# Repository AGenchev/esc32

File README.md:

# code taken from esc32, reworked to compile with GCC/freeware toolchain

I modified this and reformed the project... The goal - to compile with FOSS tools completely and to contain all source.
I put in a PCB hardware design to test it.
I probably have introduced new bugs.

First "problem": When I compiled with GCC, I got less CPU free time than the binary from esc32. Thus the control loop was closer to take 100% of the CPU time.
I considered this dangerous, because the control loop is timer-driven, e.t. in IRQ. Resolution path taken: to rewrite the control loop in integer. Most of it's done, RPM calculation is still in floating point though.

The ESC code is in <a href=https://github.com/AGenchev/esc32/tree/gelemod02/onboard>"onboard"</a> directory. <br/>
The <a href=https://github.com/AGenchev/esc32/tree/gelemod02/ground>"ground"</a> directory contains the utility which tunes the rpm PID and the current limiter PID. It does not work yet with my hardware as I have not modified it. Actually I use the ESC with current limiter turned off.

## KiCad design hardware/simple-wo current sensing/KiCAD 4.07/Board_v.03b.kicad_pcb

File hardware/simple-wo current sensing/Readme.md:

This was designed for a friend who wanted simplest design. Current sensing amplifier and shunt were removed.

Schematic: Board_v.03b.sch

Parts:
C1, C2, C6, C7, C13: 10uF/25v; MICROBUILDER__0805MP
C3: 100n; MICROBUILDER__0805MP
C4, C9, C10, C14: 100n; MICROBUILDER__0603MP
C5, C11, C15: 4.7uF/25v; MICROBUILDER__0805MP
C8, C12, C16: 10nF; MICROBUILDER__0805MP
C20: 4.7u; MICROBUILDER__0805MP
D1: 1N4007 sma; do214ac
D2, D3, D4: SCHOTTKY B0540W@SOD123; sod123
IC1, IC2, IC5: IR2110S; soic-16
J1: J40MM; GELE_V04_J40MM
J3: J5MM; JUMPER_05
J4, J5, J11: J15MM; JUMPER_15
J9: J10MM; JUMPER_10
J14, J15: GELE_V05_CON-20PIN-SMD-MANUALLY-BENT-FROM-NON-SMD
PHASE_C42: PHASE_C; STEVEMARPLE_PAD
R1, R2, R10, R21, R22: 8.2Ω; MICROBUILDER__0805MP
R3, R11, R23: 15kΩ 1%; MICROBUILDER__0805MP
R5, R6, R13, R14, R25, R26: 10kΩ; MICROBUILDER__0805MP
R7, R15, R27: 2.2kΩ 1%; MICROBUILDER__0805MP
R8, R20: 0; MICROBUILDER__0805MP
R9: 8.2; MICROBUILDER__0805MP
R28: 0Ω; MICROBUILDER__0805MP
R35: 10kΩ 1%; MICROBUILDER__0805MP
R36: 1.5kΩ 1%; MICROBUILDER__0805MP
U1: 78L05F; sot89
U$1, U$10, U$16: IRF8313; so-8
U$11, U$30: CON_HEADER_1X20; GELE.TMP_M1X20_SMD_2.54MM_0.1%5c%22_LONGTRACKS
U$36: BLUEPILL; MAPLEMINI_40-DIP-BLUE-PIL
VP_0, VP_1, VP_2, VP_3, VP_4, VP_5, VP_6, VP_7, VP_8, VP_9, VP_10, VP_11: VPDEV0; VPAD_VPAC0
V_MOTOR42: V_MOTOR; STEVEMARPLE_PAD

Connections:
/+5VSB: D1.1 (A), J15.18, U1.1 (VOUT), U$36.P$38 (5V)
/A_HIGH: IC2.12 (HIN), J15.14, U$36.P$34 (PB6/SCL1)
/A_LOW: IC2.14 (LIN), J14.12, U$36.P$12 (PA7/A1/M0SI1)
/BEMF_PHASE_A: C16.2, J14.6, R8.1, R27.2, U$36.P$6 (PA1/A7)
/BEMF_PHASE_B: C12.2, J14.7, R11.2, R15.2, U$36.P$7 (PA2/A6/TX2)
/BEMF_PHASE_C: C8.2, J14.8, R7.2, R20.2, U$36.P$8 (PA3/A5/RX2)
/B_HIGH: J11.1, J15.15, U$36.P$35 (PB7/SDA1)
/B_HIGH_J0: IC5.12 (HIN), J11.2
/B_LOW: IC5.14 (LIN), J14.13, U$36.P$13 (PB0/A0)
/C_HIGH: IC1.12 (HIN), J15.16, U$36.P$36 (PB8)
/C_LOW: J1.1, J14.14, U$36.P$14 (PB1)
/C_LOW_J1: IC1.14 (LIN), J1.2
/DEV_SEL: J15.5, U$30.20, U$36.P$25 (PA8)
/HS_FL.SUP_A: C15.1, D4.2 (K), IC2.7 (VB)
/HS_FL.SUP_B: C11.1, D2.2 (K), IC5.7 (VB)
/HS_FL.SUP_C_: C5.1, D3.2 (K), IC1.7 (VB)
/N$1: R1.2, R5.2, U$1.4 (G)
/N$2: J3.2, R9.1
/N$3: R2.2, R6.1, U$1.2 (G)
/N$4: IC1.8 (HO), R1.1
/N$5: IC1.1 (LO), R2.1
/N$7: R8.2, R23.2
/N$8: R3.2, R20.1
/N$9: R9.2, R13.2, U$16.4 (G)
/N$10: IC5.8 (HO), J3.1
/N$11: R10.2, R14.1, U$16.2 (G)
/N$12: J4.2, R10.1
/N$13: IC5.1 (LO), J4.1
/N$17: R21.2, R25.2, U$10.4 (G)
/N$18: R22.2, R26.1, U$10.2 (G)
/N$19: IC2.8 (HO), R21.1
/N$20: R22.1, R28.2
/N$23: IC2.1 (LO), R28.1
/N$25: J14.5, U$36.P$5 (PA0/A8)
/N$27: J9.1, R35.2
/N$34: J14.1, U$36.P$1 (VBAT)
/N$35: J14.2, U$36.P$2 (PC13)
/N$36: J14.3, U$36.P$3 (PC14)
/N$37: J14.4, U$36.P$4 (PC15)
/N$38: J14.11, U$36.P$11 (PA6/A2/MISO1)
/N$39: J14.15, U$36.P$15 (PB10/TX3/SCL2)
/N$40: J14.16, U$36.P$16 (PB11/RX3/SDA2)
/N$41: J14.17, U$36.P$17 (RESET)
/N$43: J15.1, U$36.P$21 (PB12/SS2)
/N$44: J15.2, U$36.P$22 (PB13/SCK2)
/N$45: J15.3, U$36.P$23 (PB14/MIS02)
/N$46: J15.4, U$36.P$24 (PB15/MOSI2)
/N$48: J15.8, U$36.P$28 (PA11/USB-)
/N$49: J15.9, U$36.P$29 (PA12/USB+)
/N$50: J15.10, U$36.P$30 (PA15)
/N$51: J15.11, U$36.P$31 (PB3)
/N$52: J15.12, U$36.P$32 (PB4)
/N$53: J15.13, U$36.P$33 (PB5)
/N$54: J15.17, U$36.P$37 (PB9)
/N$55: J15.20, U$36.P$40 (3V3/1)
/PHASE_A: C15.2, IC2.6 (VS), PHASE_C42.1, R23.1, R25.1, U$10.3 (S), U$10.7 (D), U$10.8 (D), U$30.15, U$30.16
/PHASE_B: J5.2, R13.1, U$16.3 (S), U$16.7 (D), U$16.8 (D), U$30.8, U$30.9
/PHASE_BJ: C11.2, IC5.6 (VS), J5.1, R11.1
/PHASE_C: C5.2, IC1.6 (VS), R3.1, R5.1, U$1.3 (S), U$1.7 (D), U$1.8 (D), U$30.5, U$30.6
/RXD: J15.7, U$30.18, U$36.P$27 (PA10/RX1)
/SENSE_CURRENT_PA5: J14.10, U$36.P$10 (PA5/A3/SCK1)
/SENSE_VIN: J9.2, J14.9, R36.1, U$36.P$9 (PA4/A4/SS1)
/TXD: J15.6, U$30.19, U$36.P$26 (PA9/TX1)
/VCC3.3V: J14.18, U$36.P$18 (3V3)
/VDD_LOGIC_5V: C3.2, C9.2, C20.2, D1.2 (K), IC1.11 (VDD), IC2.11 (VDD), IC5.11 (VDD)
/V_MOTOR: C1.2, C2.2, C4.2, C6.1, C7.1, C10.2, C13.2, C14.2, D2.1 (A), D3.1 (A), D4.1 (A), IC1.3 (VCC), IC2.3 (VCC), IC5.3 (VCC), R35.1, U1.3 (VIN), U$1.5 (D), U$1.6 (D), U$10.5 (D), U$10.6 (D), U$16.5 (D), U$16.6 (D), U$30.13, U$30.14, V_MOTOR42.1
GND: C1.1, C2.1, C3.1, C4.1, C6.2, C7.2, C8.1, C9.1, C10.1, C12.1, C13.1, C14.1, C16.1, C20.1, IC1.2 (COM), IC1.13 (~SD), IC1.15 (VSS), IC2.2 (COM), IC2.13 (~SD), IC2.15 (VSS), IC5.2 (COM), IC5.13 (~SD), IC5.15 (VSS), J14.19, J14.20, J15.19, R6.2, R7.1, R14.2, R15.1, R26.2, R27.1, R36.2, U1.2 (REF), U$1.1 (S), U$10.1 (S), U$11.1, U$11.2, U$11.3, U$11.4, U$11.5, U$11.6, U$11.7, U$11.8, U$11.9, U$11.10, U$11.11, U$11.12, U$11.13, U$11.14, U$11.15, U$11.16, U$11.17, U$11.18, U$11.19, U$11.20, U$16.1 (S), U$30.1, U$30.2, U$30.11, U$30.12, U$30.17, U$36.P$19 (GND/1), U$36.P$20 (GND/2), U$36.P$39 (GND/3), VP_0.VP, VP_1.VP, VP_2.VP, VP_3.VP, VP_4.VP, VP_5.VP, VP_6.VP, VP_7.VP, VP_8.VP, VP_9.VP, VP_10.VP, VP_11.VP

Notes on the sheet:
Drawn at Grid = 0.635 mm = 0.025inch
It was for per phase current sens. R=0.0203 Ω PCB FR4 1 oz = 0.035 mm W=0.406 mm L=17 mm

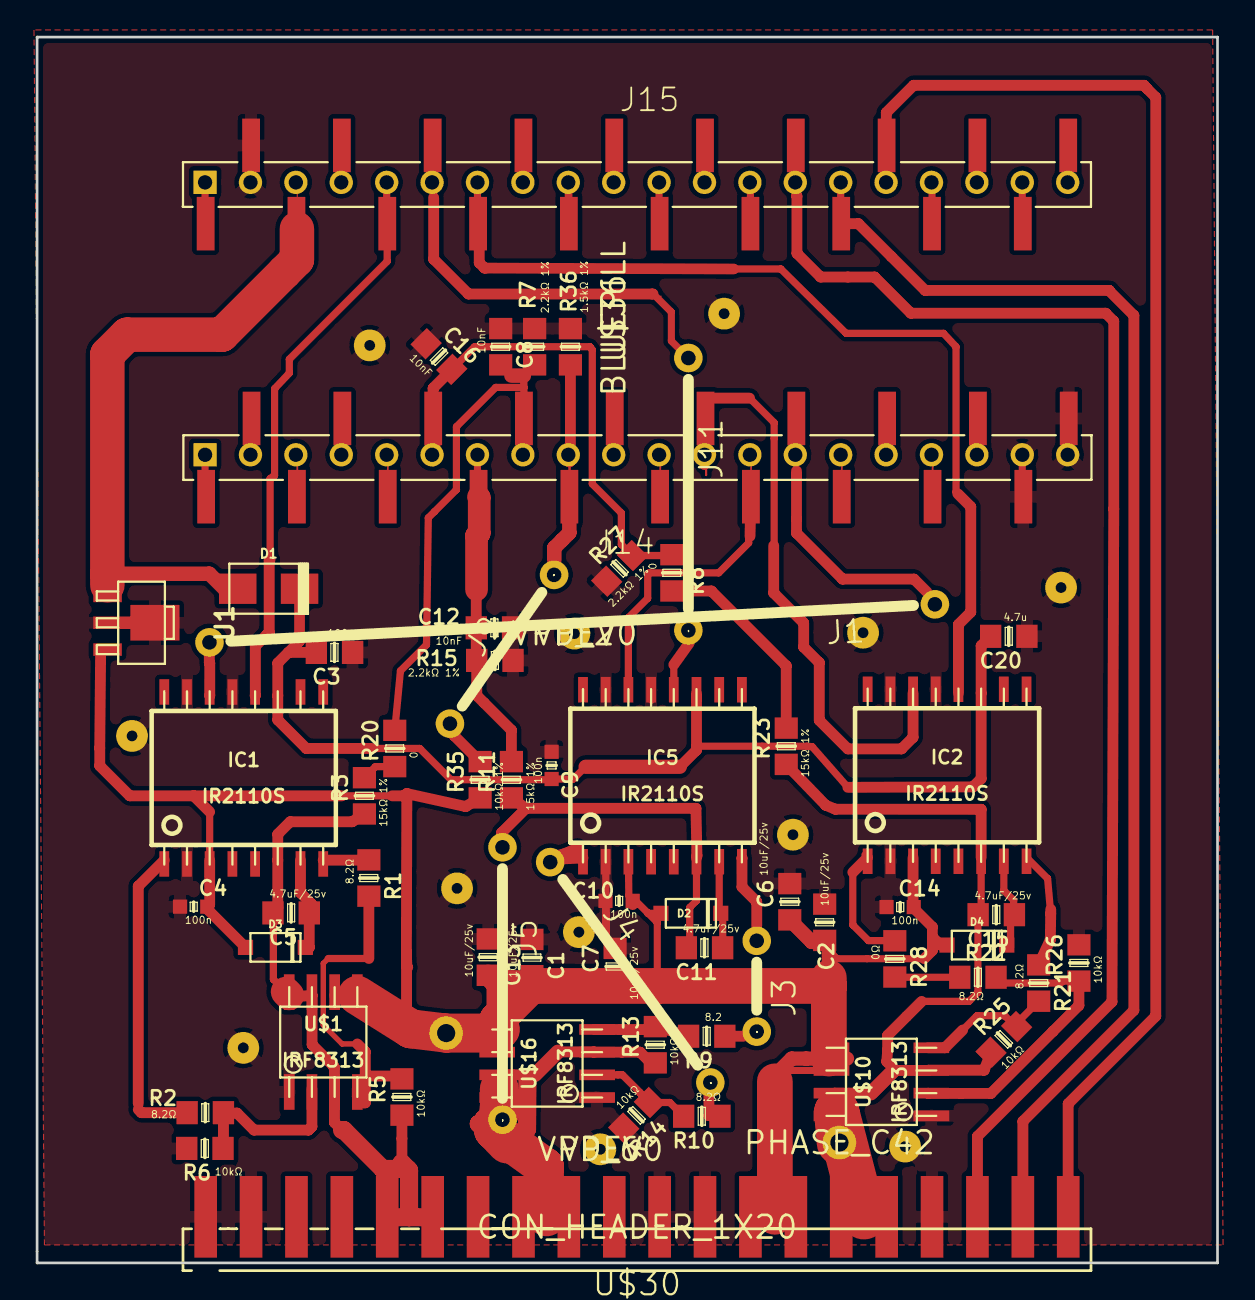
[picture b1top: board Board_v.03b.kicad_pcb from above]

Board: 2 copper layers, 66.0 x 68.6 mm, 76 parts (0 on the bottom side), 67 nets.

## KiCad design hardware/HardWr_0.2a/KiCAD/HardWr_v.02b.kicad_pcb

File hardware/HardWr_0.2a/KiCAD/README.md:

<h1>Converted to KiCAD</h1>

Library used: https://github.com/JorgeAparicio/libKiCad

For 3D rendering to work, i had to edit '/home/username/.config/kicad/kicad_common' ini file<br/>
the format is ini file, section is [EnvironmentVariables]<br/>
entry is:<br/>
<b>LIBKICAD=/full_path_to_libkicad_main_folder/</b>

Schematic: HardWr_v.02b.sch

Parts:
BLUEPILL-STM32F103C8T6_MODULE1: BLUEPILL; MAPLEMINI_40-DIP-BLUE-PIL
C1, C2, C6, C7, C13: 10uF/25v; c_0805
C3, C4, C18: 100n; c_0805
C5, C11, C15: 4.7uF/25v; c_0805
C8, C12, C16: 10nF; c_0805
C9, C10, C14: 100n; c_0603
C19: 1u; c_0805
C20: 4.7u; c_0805
D1: 1N4007 SMA; do214ac
D2, D3, D4: B0540W @ SOD123; sod123
IC1, IC2, IC5: IR2110S; soic-16
IC3: 78L05F; sot89
IC4: MCP601OT; sot23-5
J1: J35MM; GELE_V04_J35MM
J2, J3: J10MM; JUMPER_10
J4, J11: J20MM; JUMPER_20
J5: J15MM; JUMPER_15
J9: J12MM; JUMPER_12
J14, J15: GELE_V05_CON-20PIN-SMD-MANUALLY-BENT-FROM-NON-SMD
JP1: PINHEAD-2_1X04SMD
PHASE_A42: PHASE_A; STEVEMARPLE_PAD
PHASE_B42: PHASE_B; STEVEMARPLE_PAD
PHASE_C42: PHASE_C; STEVEMARPLE_PAD
R1, R2, R9, R10, R21, R22: 8.2Ω; r_0805
R3, R11, R23: 15kΩ 1%; r_0805
R4, R8, R24: 0; r_0805
R5, R6, R13, R14, R25, R26: 10kΩ; r_0805
R7, R15, R27: 2.2kΩ 1%; r_0805
R12, R16, R20, R28: 0Ω; r_0805
R29, R33: 11kΩ 1%; r_0805
R31: 20mΩ|0.02Ω 1%; r_2512
R32, R37: 91Ω 1%; r_0805
R34: 600Ω; r_0805
R35: 10kΩ 1%; r_0805
R36: 1.5kΩ 1%; r_0805
U$1, U$10, U$16: IRF8313; so-8
VP_0, VP_1, VP_2, VP_3, VP_4, VP_5, VP_6, VP_7, VP_8, VP_9, VP_10, VP_11, VP_12: VPDEV0; VPAD_VPAC0
V_MOTOR42: V_MOTOR; STEVEMARPLE_PAD

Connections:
/+5VSB: BLUEPILL-STM32F103C8T6_MODULE1.P$38 (5V), D1.1 (A), IC3.1 (VO), J15.18
/A_HIGH: BLUEPILL-STM32F103C8T6_MODULE1.P$34 (PB6/SCL1), IC2.12 (HIN), J15.14
/A_LOW: BLUEPILL-STM32F103C8T6_MODULE1.P$12 (PA7/A1/M0SI1), J14.12, R16.2
/BEMF_PHASE_A: BLUEPILL-STM32F103C8T6_MODULE1.P$6 (PA1/A7), C16.2, J14.6, R8.1, R27.2
/BEMF_PHASE_B: BLUEPILL-STM32F103C8T6_MODULE1.P$7 (PA2/A6/TX2), C12.2, J14.7, R11.2, R15.2
/BEMF_PHASE_C: BLUEPILL-STM32F103C8T6_MODULE1.P$8 (PA3/A5/RX2), C8.2, J14.8, R7.2, R20.2
/B_HIGH: BLUEPILL-STM32F103C8T6_MODULE1.P$35 (PB7/SDA1), J11.1, J15.15
/B_HIGH_J0: IC5.12 (HIN), J11.2
/B_LOW: BLUEPILL-STM32F103C8T6_MODULE1.P$13 (PB0/A0), IC5.14 (LIN), J14.13
/C_HIGH: BLUEPILL-STM32F103C8T6_MODULE1.P$36 (PB8), IC1.12 (HIN), J15.16
/C_LOW: BLUEPILL-STM32F103C8T6_MODULE1.P$14 (PB1), J1.1, J14.14
/C_LOW_J1: IC1.14 (LIN), J1.2
/HS_FL.SUP_A: C15.1, D4.2 (K), IC2.7 (VB)
/HS_FL.SUP_B: C11.1, D2.2 (K), IC5.7 (VB)
/HS_FL.SUP_C_: C5.1, D3.2 (K), IC1.7 (VB)
/N$1: R1.2, R5.2, U$1.4 (G)
/N$2: J3.2, R9.1
/N$3: R2.2, R6.1, U$1.2 (G)
/N$4: IC1.8 (HO), R1.1
/N$5: J2.2, R2.1
/N$6: IC1.1 (LO), J2.1
/N$7: R8.2, R23.2
/N$8: R3.2, R20.1
/N$9: R9.2, R13.2, U$16.4 (G)
/N$10: IC5.8 (HO), J3.1
/N$11: R10.2, R14.1, U$16.2 (G)
/N$12: J4.2, R10.1
/N$13: IC5.1 (LO), J4.1
/N$14: IC4.4 (-IN), R32.2, R33.1
/N$17: R21.2, R25.2, U$10.4 (G)
/N$18: R22.2, R26.1, U$10.2 (G)
/N$19: IC2.8 (HO), R21.1
/N$20: R22.1, R28.2
/N$23: IC2.1 (LO), R28.1
/N$24: IC4.1 (OUT), R33.2, R34.1
/N$25: BLUEPILL-STM32F103C8T6_MODULE1.P$5 (PA0/A8), J14.5
/N$26: IC2.14 (LIN), R16.1
/N$27: J9.1, R35.2
/N$30: BLUEPILL-STM32F103C8T6_MODULE1.P$26 (PA9/TX1), J15.6, JP1.2
/N$31: BLUEPILL-STM32F103C8T6_MODULE1.P$27 (PA10/RX1), J15.7, JP1.1
/N$32: IC4.3 (+IN), R29.1, R37.1
/N$34: BLUEPILL-STM32F103C8T6_MODULE1.P$1 (VBAT), J14.1
/N$35: BLUEPILL-STM32F103C8T6_MODULE1.P$2 (PC13), J14.2
/N$36: BLUEPILL-STM32F103C8T6_MODULE1.P$3 (PC14), J14.3
/N$37: BLUEPILL-STM32F103C8T6_MODULE1.P$4 (PC15), J14.4
/N$38: BLUEPILL-STM32F103C8T6_MODULE1.P$11 (PA6/A2/MISO1), J14.11
/N$39: BLUEPILL-STM32F103C8T6_MODULE1.P$15 (PB10/TX3/SCL2), J14.15
/N$40: BLUEPILL-STM32F103C8T6_MODULE1.P$16 (PB11/RX3/SDA2), J14.16
/N$41: BLUEPILL-STM32F103C8T6_MODULE1.P$17 (RESET), J14.17
/N$43: BLUEPILL-STM32F103C8T6_MODULE1.P$21 (PB12/SS2), J15.1
/N$44: BLUEPILL-STM32F103C8T6_MODULE1.P$22 (PB13/SCK2), J15.2
/N$45: BLUEPILL-STM32F103C8T6_MODULE1.P$23 (PB14/MIS02), J15.3
/N$46: BLUEPILL-STM32F103C8T6_MODULE1.P$24 (PB15/MOSI2), J15.4
/N$47: BLUEPILL-STM32F103C8T6_MODULE1.P$25 (PA8), J15.5, JP1.4
/N$48: BLUEPILL-STM32F103C8T6_MODULE1.P$28 (PA11/USB-), J15.8
/N$49: BLUEPILL-STM32F103C8T6_MODULE1.P$29 (PA12/USB+), J15.9
/N$50: BLUEPILL-STM32F103C8T6_MODULE1.P$30 (PA15), J15.10
/N$51: BLUEPILL-STM32F103C8T6_MODULE1.P$31 (PB3), J15.11
/N$52: BLUEPILL-STM32F103C8T6_MODULE1.P$32 (PB4), J15.12
/N$53: BLUEPILL-STM32F103C8T6_MODULE1.P$33 (PB5), J15.13
/N$54: BLUEPILL-STM32F103C8T6_MODULE1.P$37 (PB9), J15.17
/N$55: BLUEPILL-STM32F103C8T6_MODULE1.P$40 (3V3/1), J15.20
/PHASE_A: C15.2, IC2.6 (VS), PHASE_C42.1, R23.1, R25.1, U$10.3 (S), U$10.7 (D), U$10.8 (D)
/PHASE_B: J5.2, PHASE_B42.1, R13.1, U$16.3 (S), U$16.7 (D), U$16.8 (D)
/PHASE_BJ: C11.2, IC5.6 (VS), J5.1, R11.1
/PHASE_C: C5.2, IC1.6 (VS), PHASE_A42.1, R3.1, R5.1, U$1.3 (S), U$1.7 (D), U$1.8 (D)
/SENSE_CURRENT_PA5: BLUEPILL-STM32F103C8T6_MODULE1.P$10 (PA5/A3/SCK1), C19.2, J14.10, R34.2
/SENSE_VIN: BLUEPILL-STM32F103C8T6_MODULE1.P$9 (PA4/A4/SS1), J9.2, J14.9, R36.1
/TOT_CURRENT: C6.2, C7.2, R6.2, R14.2, R26.2, R31.1, R37.2, U$1.1 (S), U$10.1 (S), U$16.1 (S)
/VCC3.3V: BLUEPILL-STM32F103C8T6_MODULE1.P$18 (3V3), C18.2, IC4.5 (V+), J14.18
/VDD_LOGIC_4.4V: C3.2, C9.2, C20.2, D1.2 (K), IC1.11 (VDD), IC2.11 (VDD), IC5.11 (VDD)
/V_MOTOR: C1.2, C2.2, C4.2, C6.1, C7.1, C10.2, C13.2, C14.2, D2.1 (A), D3.1 (A), D4.1 (A), IC1.3 (VCC), IC2.3 (VCC), IC3.3 (VI), IC5.3 (VCC), R35.1, U$1.5 (D), U$1.6 (D), U$10.5 (D), U$10.6 (D), U$16.5 (D), U$16.6 (D), V_MOTOR42.1
/~SHDN_A_: IC2.13 (~SD), R24.2
/~SHDN_B: IC5.13 (~SD), R12.2
/~SHDN_C_: IC1.13 (~SD), R4.2
GND: BLUEPILL-STM32F103C8T6_MODULE1.P$19 (GND/1), BLUEPILL-STM32F103C8T6_MODULE1.P$20 (GND/2), BLUEPILL-STM32F103C8T6_MODULE1.P$39 (GND/3), C1.1, C2.1, C3.1, C4.1, C8.1, C9.1, C10.1, C12.1, C13.1, C14.1, C16.1, C18.1, C19.1, C20.1, IC1.2 (COM), IC1.15 (VSS), IC2.2 (COM), IC2.15 (VSS), IC3.2 (GND), IC4.2 (V-), IC5.2 (COM), IC5.15 (VSS), J14.19, J14.20, J15.19, JP1.3, R4.1, R7.1, R12.1, R15.1, R24.1, R27.1, R29.2, R31.2, R32.1, R36.2, VP_0.VP, VP_1.VP, VP_2.VP, VP_3.VP, VP_4.VP, VP_5.VP, VP_6.VP, VP_7.VP, VP_8.VP, VP_9.VP, VP_10.VP, VP_11.VP, VP_12.VP

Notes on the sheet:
Drawn at Grid = 0.635 mm = 0.025inch
It was for per phase current sens. R=0.0203 Ω PCB FR4 1 oz = 0.035 mm W=0.406 mm L=17 mm
Kamp need=~127 times for 0.02Ω shunt, Kamp=~51times for 0.05Ω|50mΩ shunt PCB Shunt 0.0203 Ω at PCB FR4 ,1 oz = 0.035 mm W=0.406 mm L=17 mm Kamp=(R29/R32) - see classical difference amplifier sch
The opamp should be w. lowest possible offset. Some of them: TLC277
Notes: Since Vmotor is tied to Vcc of the mosfet drivers IR2110, it can not exceed the IR2110 max Vcc (20V) Used protocol: CLI via Serial port at 262400 kbit/s on JP1. PWM protocol has been turned off as I need to control it via serial port. - PA8 is used as "Controller select" e.t. to listen comma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

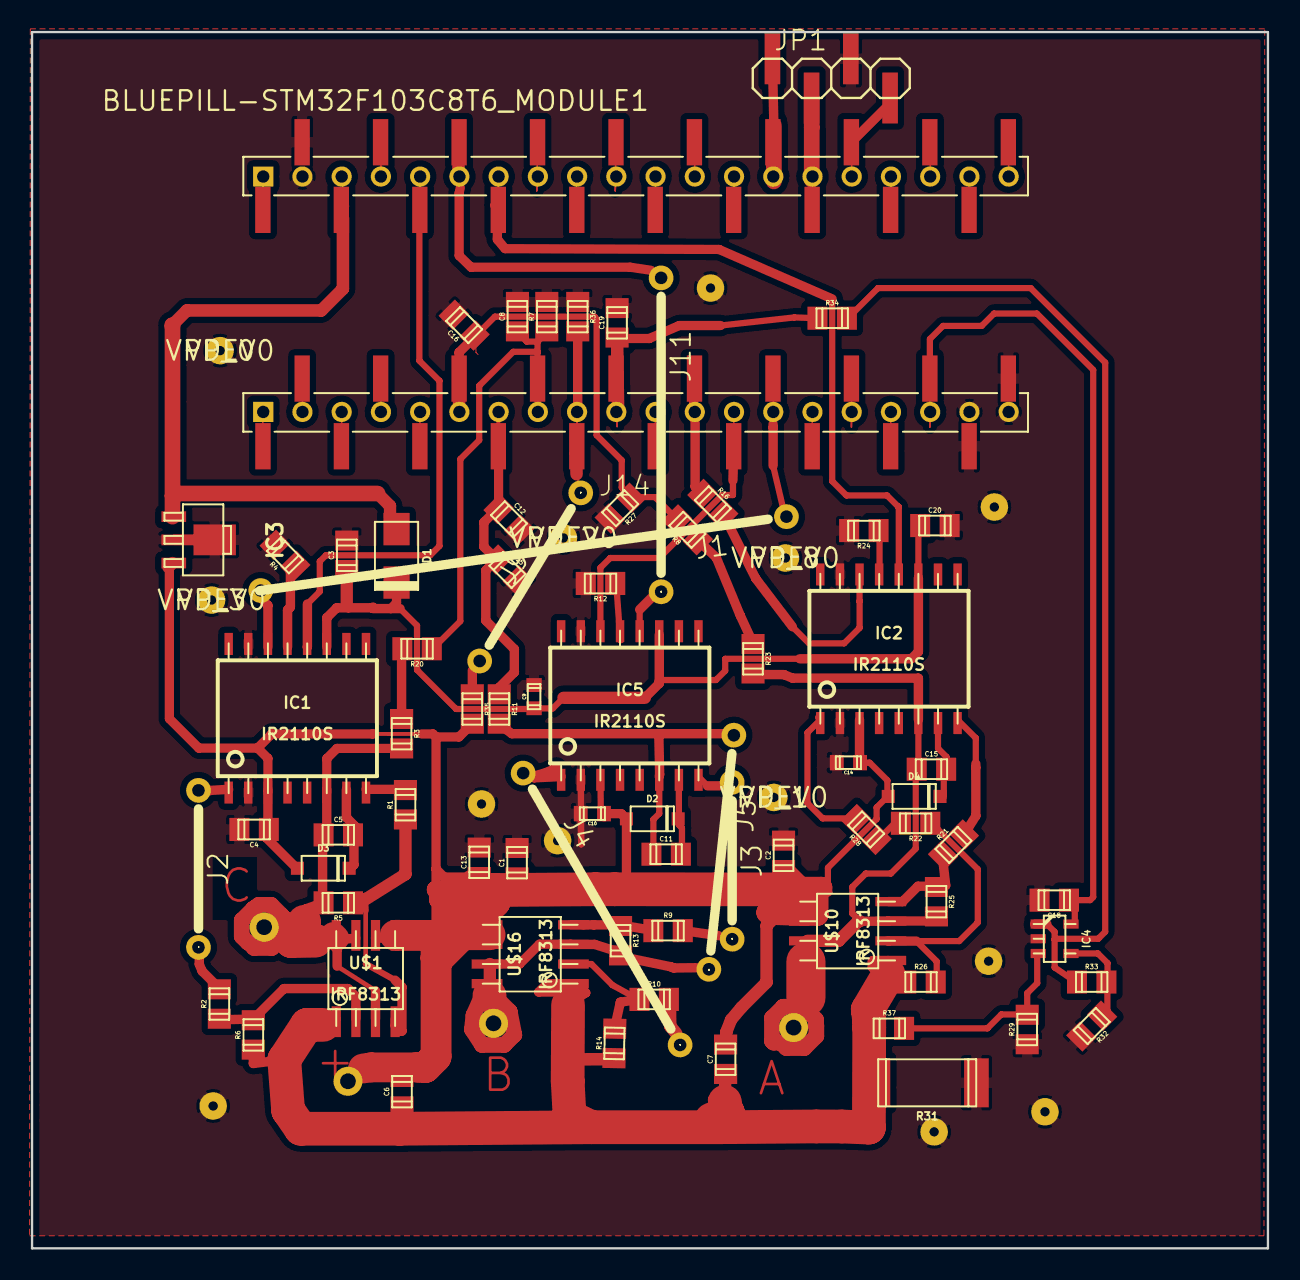
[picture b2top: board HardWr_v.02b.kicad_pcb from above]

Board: 2 copper layers, 80.0 x 78.7 mm, 92 parts (0 on the bottom side), 76 nets.

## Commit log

2017-11-25 Different makefile
    Compiles the ESC firmware with a GNU arm-none-eabi toolchain.
2017-11-25 Rename onboard/adc.c to onboard/src/adc.c
2017-11-25 Rename onboard/adc.h to onboard/src/adc.h
2017-11-25 Refactoring of the project to have cleaner layout
2017-11-25 Refactoring
2017-11-25 Code rework. Add all necessary routines to compile w GCC
2018-02-25 Create empty
2018-02-25 Update Readme.md
    added hardware schematics
2018-02-25 Update README.md
    fixed typo
2018-03-01 Update README.md
    reflect things as of 1 March 2018
2018-03-01 Synced code with my latest experiments
2018-03-03 Update Makefile

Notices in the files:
parts and their libraries:
microbuilder: This work is placed in the public domain, and may be freely used for commercial and non-commercial work with the following conditions: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
